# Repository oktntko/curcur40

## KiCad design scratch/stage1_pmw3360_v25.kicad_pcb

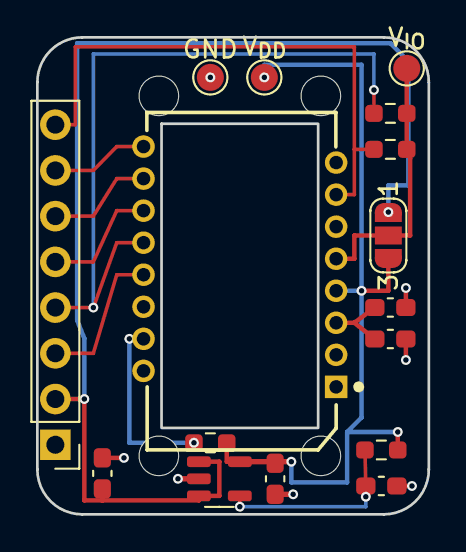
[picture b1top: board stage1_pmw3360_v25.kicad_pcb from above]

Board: 2 copper layers, 21.8 x 26.5 mm, 20 parts (0 on the bottom side), 13 nets.

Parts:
C1: 4.7uF/10V; C_0603_1608Metric_Pad1.08x0.95mm_HandSolder
C2: 100nF; C_0603_1608Metric_Pad1.08x0.95mm_HandSolder
C3, C4: 1uF; C_0603_1608Metric_Pad1.08x0.95mm_HandSolder
C5: 22nF; C_0603_1608Metric_Pad1.08x0.95mm_HandSolder
H1, H2, H3, H4: MountingHole_2.2mm_M2
J1: Conn_01x08; PinHeader_1x08_P2.54mm_Vertical
JP1: SolderJumper_3_Open; SolderJumper-3_P1.3mm_Open_RoundedPad1.0x1.5mm_NumberLabels
R1, R2: 10k; R_0603_1608Metric_Pad0.98x0.95mm_HandSolder
R3: 39R; R_0603_1608Metric_Pad0.98x0.95mm_HandSolder
R4: 28k; R_0603_1608Metric_Pad0.98x0.95mm_HandSolder
TP1: VIO; TestPoint_Pad_D1.5mm
TP2: VDD; TestPoint_Pad_D1.5mm
TP3: GND; TestPoint_Pad_D1.5mm
U1: PMW3360DM-T2QU; PMW3360DM-T2QU_16Pin
U2: TLV74318PDBVR; SOT-23-5

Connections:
/CS: J1.3, U1.13 (~CS)
/MISO: J1.4, R2.2, U1.12 (MISO)
/MOSI: J1.5, U1.11 (MOSI)
/MOTION: J1.7, U1.9 (MOTION)
/RESET: J1.8, R1.2, U1.7 (~RESET)
/SCLK: J1.6, U1.10 (SCLK)
GND: C1.2, C2.2, C3.2, C4.2, C5.2, J1.1, TP3.1, U1.8 (GND), U2.2 (GND)
unnamed: R3.2, U1.15 (LED_P)
unnamed: C1.1, C2.1, U1.3 (VDDPIX)
unnamed: C5.1, R4.2, U2.4 (NC)
VDD: C4.1, JP1.3 (B), R3.1, R4.1, TP2.1, U1.4 (VDD), U2.5 (OUT)
V_{IN}: C3.1, J1.2, JP1.1 (A), U2.1 (IN), U2.3 (EN)
V_{IO}: JP1.2 (C), R1.1, R2.1, TP1.1, U1.5 (VDDIO)

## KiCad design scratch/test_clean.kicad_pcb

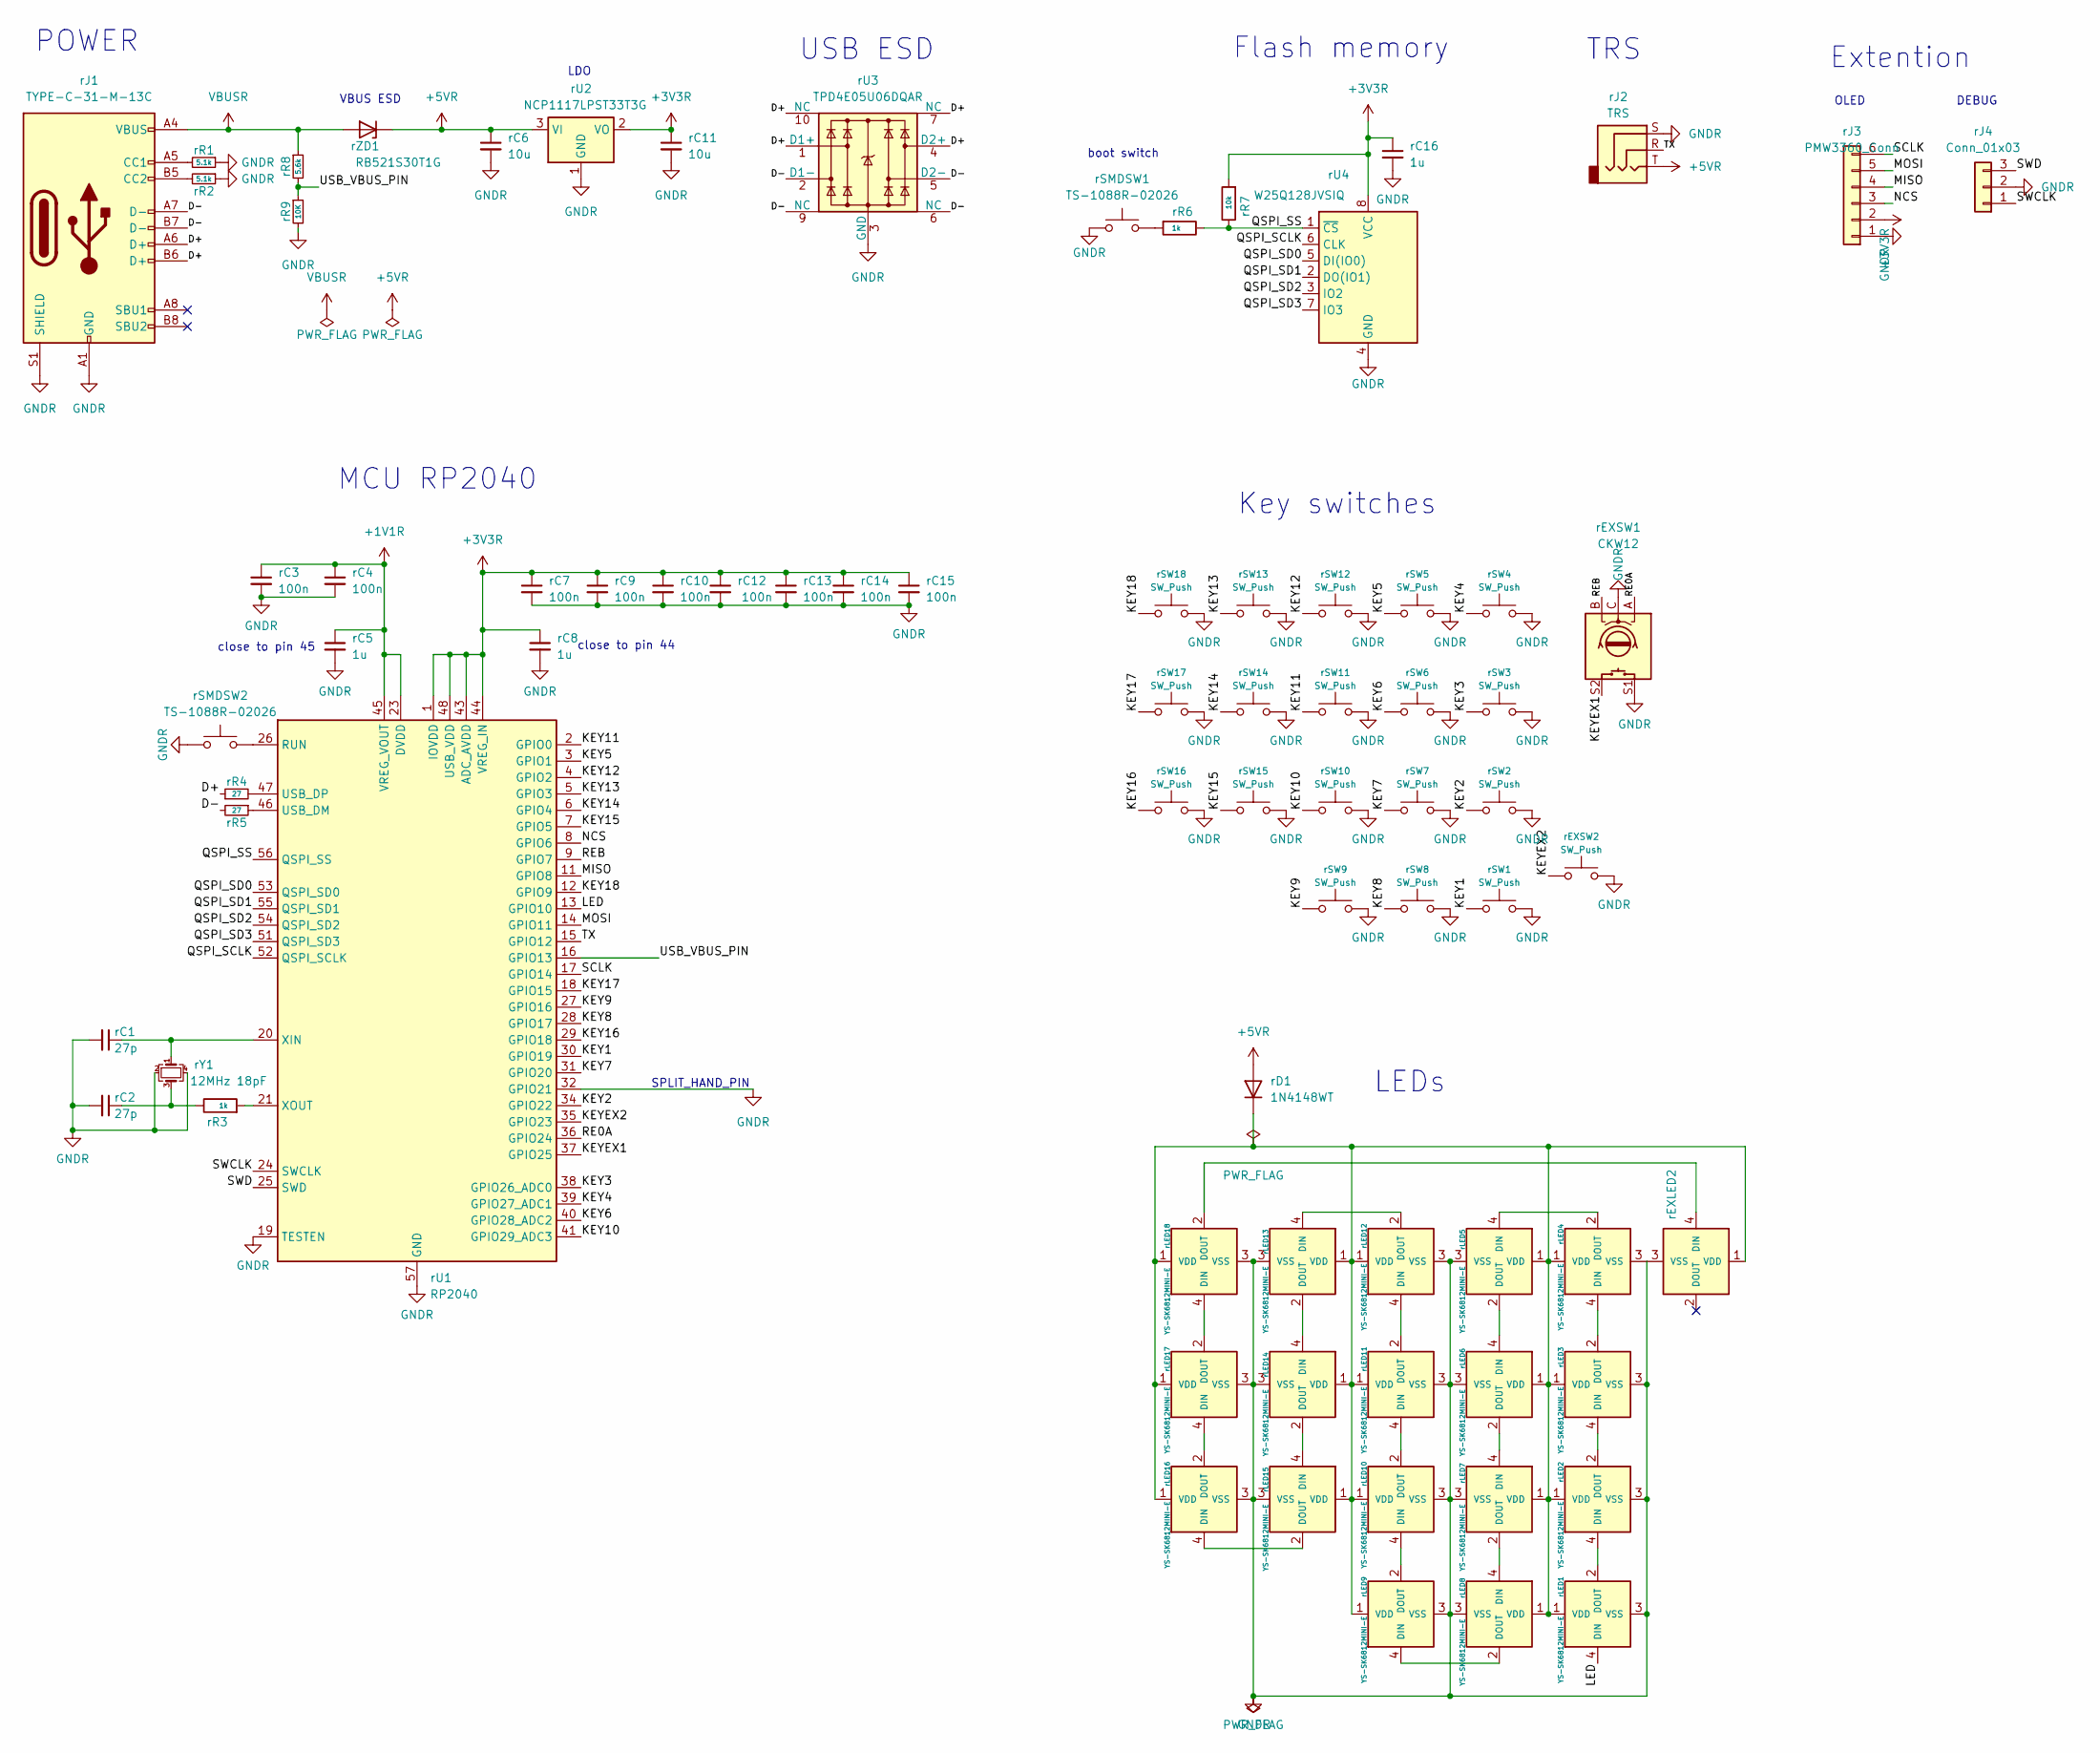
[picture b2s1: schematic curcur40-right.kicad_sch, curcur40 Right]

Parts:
rC1, rC2: 27p; C_0402_1005Metric
rC3, rC4, rC7, rC9, rC10, rC12, rC13, rC14, rC15: 100n; C_0402_1005Metric
rC5, rC8, rC16: 1u; C_0402_1005Metric
rC6, rC11: 10u; C_0402_1005Metric
rD1: 1N4148WT; D_SOD-523; JLCPCB Part # C232841
rEXLED2: YS-SK6812MINI-E
rEXSW1: CKW12
rEXSW2: SW_Push; keyswitch_choc12_hotswap_1u
rJ1: TYPE-C-31-M-13C; JLCPCB Part # C2848620
rJ2: TRS; PJ-398A-5A_PJ-399B-6A; JLCPCB Part # C128994
rJ3: PMW3360_Conn; PinHeader_1x06_P2.54mm_Vertical
rJ4: Conn_01x03; PinHeader_1x03_P2.54mm_Vertical
rLED1, rLED2, rLED3, rLED4, rLED5, rLED6, rLED7, rLED8, rLED9, rLED10, rLED11, rLED12, rLED13, rLED14, rLED15, rLED16, rLED17, rLED18: YS-SK6812MINI-E
rR1, rR2: 5.1k; R_0402_1005Metric
rR3, rR6: 1k; R_0402_1005Metric
rR4, rR5: 27; R_0402_1005Metric
rR7: 10k; R_0402_1005Metric
rR8: 5.6k; R_0402_1005Metric
rR9: 10K; R_0402_1005Metric
rSMDSW1, rSMDSW2: TS-1088R-02026; JLCPCB Part # C455280
rSW1, rSW2, rSW3, rSW4, rSW5, rSW6, rSW7, rSW8, rSW9, rSW10, rSW11, rSW12, rSW13, rSW14, rSW15, rSW16, rSW17, rSW18: SW_Push; keyswitch_choc12_hotswap_1u
rU1: RP2040; QFN-56-1EP_7x7mm_P0.4mm_EP3.2x3.2mm; JLCPCB Part # C2040
rU2: NCP1117LPST33T3G; SOT-223-3_TabPin2; JLCPCB Part # C146799
rU3: TPD4E05U06DQAR; USON-10_2.5x1.0mm_P0.5mm; JLCPCB Part # C138714
rU4: W25Q128JVSIQ; SOIC-8_5.3x5.3mm_P1.27mm; JLCPCB Part # C113767
rY1: 12MHz 18pF; Crystal_SMD_3225-4Pin_3.2x2.5mm; MFR.Part # Q22FA23V0041800; JLCPCB Part # C91749
rZD1: RB521S30T1G; D_SOD-523; JLCPCB Part # C145179

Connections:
+1V1R: rC3.1, rC4.1, rC5.1, rU1.23 (DVDD), rU1.45 (VREG_VOUT), rU1.50 (DVDD)
+3V3R: rC7.1, rC8.1, rC9.1, rC10.1, rC11.1, rC12.1, rC13.1, rC14.1, rC15.1, rC16.1, rJ3.2, rR7.2, rU1.1 (IOVDD), rU1.10 (IOVDD), rU1.22 (IOVDD), rU1.33 (IOVDD), rU1.42 (IOVDD), rU1.43 (ADC_AVDD), rU1.44 (VREG_IN), rU1.48 (USB_VDD), rU1.49 (IOVDD), rU2.2 (VO), rU4.8 (VCC); also elsewhere on the board
+5VR: rC6.1, rD1.2 (A), rJ2.T, rU2.3 (VI), rZD1.1 (K)
/D+: rJ1.A6 (D+), rJ1.B6 (D+), rR4.1, rU3.1 (D1+), rU3.4 (D2+), rU3.7 (NC), rU3.10 (NC)
/D-: rJ1.A7 (D-), rJ1.B7 (D-), rR5.2, rU3.2 (D1-), rU3.5 (D2-), rU3.6 (NC), rU3.9 (NC)
/KEY1: rSW1.1, rU1.30 (GPIO19)
/KEY2: rSW2.1, rU1.34 (GPIO22)
/KEY3: rSW3.1, rU1.38 (GPIO26_ADC0)
/KEY4: rSW4.1, rU1.39 (GPIO27_ADC1)
/KEY5: rSW5.1, rU1.3 (GPIO1)
/KEY6: rSW6.1, rU1.40 (GPIO28_ADC2)
/KEY7: rSW7.1, rU1.31 (GPIO20)
/KEY8: rSW8.1, rU1.28 (GPIO17)
/KEY9: rSW9.1, rU1.27 (GPIO16)
/KEY10: rSW10.1, rU1.41 (GPIO29_ADC3)
/KEY11: rSW11.1, rU1.2 (GPIO0)
/KEY12: rSW12.1, rU1.4 (GPIO2)
/KEY13: rSW13.1, rU1.5 (GPIO3)
/KEY14: rSW14.1, rU1.6 (GPIO4)
/KEY15: rSW15.1, rU1.7 (GPIO5)
/KEY16: rSW16.1, rU1.29 (GPIO18)
/KEY17: rSW17.1, rU1.18 (GPIO15)
/KEY18: rSW18.1, rU1.12 (GPIO9)
/KEYEX1: rEXSW1.S2, rU1.37 (GPIO25)
/KEYEX2: rEXSW2.1, rU1.35 (GPIO23)
/LED: rLED1.4 (DIN), rU1.13 (GPIO10)
/MISO: rJ3.4, rU1.11 (GPIO8); also elsewhere on the board
/MOSI: rJ3.5, rU1.14 (GPIO11); also elsewhere on the board
/NCS: rJ3.3, rU1.8 (GPIO6); also elsewhere on the board
/QSPI_SCLK: rU1.52 (QSPI_SCLK), rU4.6 (CLK)
/QSPI_SD0: rU1.53 (QSPI_SD0), rU4.5 (DI(IO0))
/QSPI_SD1: rU1.55 (QSPI_SD1), rU4.2 (DO(IO1))
/QSPI_SD2: rU1.54 (QSPI_SD2), rU4.3 (IO2)
/QSPI_SD3: rU1.51 (QSPI_SD3), rU4.7 (IO3)
/QSPI_SS: rR6.1, rR7.1, rU1.56 (QSPI_SS), rU4.1 (~CS)
/RE0A: rEXSW1.A, rU1.36 (GPIO24)
/REB: rEXSW1.B, rU1.9 (GPIO7)
/SCLK: rJ3.6, rU1.17 (GPIO14); also elsewhere on the board
/SWCLK: rJ4.1, rU1.24 (SWCLK)
/SWD: rJ4.3, rU1.25 (SWD)
/TX: rJ2.R, rU1.15 (GPIO12)
/USB_VBUS_PIN: rR8.2, rR9.1, rU1.16 (GPIO13)
GNDR: rC1.2, rC2.2, rC3.2, rC4.2, rC5.2, rC6.2, rC7.2, rC8.2, rC9.2, rC10.2, rC11.2, rC12.2, rC13.2, rC14.2, rC15.2, rC16.2, rEXLED2.3 (VSS), rEXSW1.C, rEXSW1.S1, rEXSW2.2, rJ1.A1 (GND), rJ1.A12 (GND), rJ1.B1 (GND), rJ1.B12 (GND), rJ1.S1 (SHIELD), rJ2.S, rJ3.1, rJ4.2, rLED1.3 (VSS), rLED2.3 (VSS), rLED3.3 (VSS), rLED4.3 (VSS), rLED5.3 (VSS), rLED6.3 (VSS), rLED7.3 (VSS), rLED8.3 (VSS), rLED9.3 (VSS), rLED10.3 (VSS), rLED11.3 (VSS), rLED12.3 (VSS), rLED13.3 (VSS), rLED14.3 (VSS), rLED15.3 (VSS), rLED16.3 (VSS), rLED17.3 (VSS), rLED18.3 (VSS), rR1.1, rR2.1, rR9.2, rSMDSW1.1, rSMDSW2.1, rSW1.2, rSW2.2, rSW3.2, rSW4.2, rSW5.2, rSW6.2, rSW7.2, rSW8.2, rSW9.2, rSW10.2, rSW11.2, rSW12.2, rSW13.2, rSW14.2, rSW15.2, rSW16.2, rSW17.2, rSW18.2, rU1.19 (TESTEN), rU1.32 (GPIO21), rU1.57 (GND), rU2.1 (GND), rU3.3 (GND), rU3.8 (GND), rU4.4 (GND), rY1.2, rY1.4; also elsewhere on the board
unnamed: rC2.1, rR3.1, rY1.3
unnamed: rD1.1 (K), rEXLED2.1 (VDD), rLED1.1 (VDD), rLED2.1 (VDD), rLED3.1 (VDD), rLED4.1 (VDD), rLED5.1 (VDD), rLED6.1 (VDD), rLED7.1 (VDD), rLED8.1 (VDD), rLED9.1 (VDD), rLED10.1 (VDD), rLED11.1 (VDD), rLED12.1 (VDD), rLED13.1 (VDD), rLED14.1 (VDD), rLED15.1 (VDD), rLED16.1 (VDD), rLED17.1 (VDD), rLED18.1 (VDD)
unnamed: rEXLED2.4 (DIN), rLED18.2 (DOUT)
unnamed: rJ1.A5 (CC1), rR1.2
unnamed: rJ1.B5 (CC2), rR2.2
unnamed: rLED1.2 (DOUT), rLED2.4 (DIN)
unnamed: rLED2.2 (DOUT), rLED3.4 (DIN)
unnamed: rLED3.2 (DOUT), rLED4.4 (DIN)
unnamed: rLED4.2 (DOUT), rLED5.4 (DIN)
unnamed: rLED5.2 (DOUT), rLED6.4 (DIN)
unnamed: rLED6.2 (DOUT), rLED7.4 (DIN)
unnamed: rLED7.2 (DOUT), rLED8.4 (DIN)
unnamed: rLED8.2 (DOUT), rLED9.4 (DIN)
unnamed: rLED9.2 (DOUT), rLED10.4 (DIN)
unnamed: rLED10.2 (DOUT), rLED11.4 (DIN)
unnamed: rLED11.2 (DOUT), rLED12.4 (DIN)
unnamed: rLED12.2 (DOUT), rLED13.4 (DIN)
unnamed: rLED13.2 (DOUT), rLED14.4 (DIN)
unnamed: rLED14.2 (DOUT), rLED15.4 (DIN)
unnamed: rLED15.2 (DOUT), rLED16.4 (DIN)
unnamed: rLED16.2 (DOUT), rLED17.4 (DIN)
unnamed: rLED17.2 (DOUT), rLED18.4 (DIN)
unnamed: rR6.2, rSMDSW1.2
unnamed: rSMDSW2.2, rU1.26 (RUN)
unnamed: rR5.1, rU1.46 (USB_DM)
unnamed: rR4.2, rU1.47 (USB_DP)
unnamed: rC1.1, rU1.20 (XIN), rY1.1
unnamed: rR3.2, rU1.21 (XOUT)
VBUSR: rJ1.A4 (VBUS), rJ1.A9 (VBUS), rJ1.B4 (VBUS), rJ1.B9 (VBUS), rR8.1, rZD1.2 (A)

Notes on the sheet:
USB ESD
TRS
Flash memory
MCU RP2040
DEBUG
POWER
boot switch
LDO
Key switches
LEDs
Extention
VBUS ESD
OLED
close to pin 45
close to pin 44
SPLIT_HAND_PIN

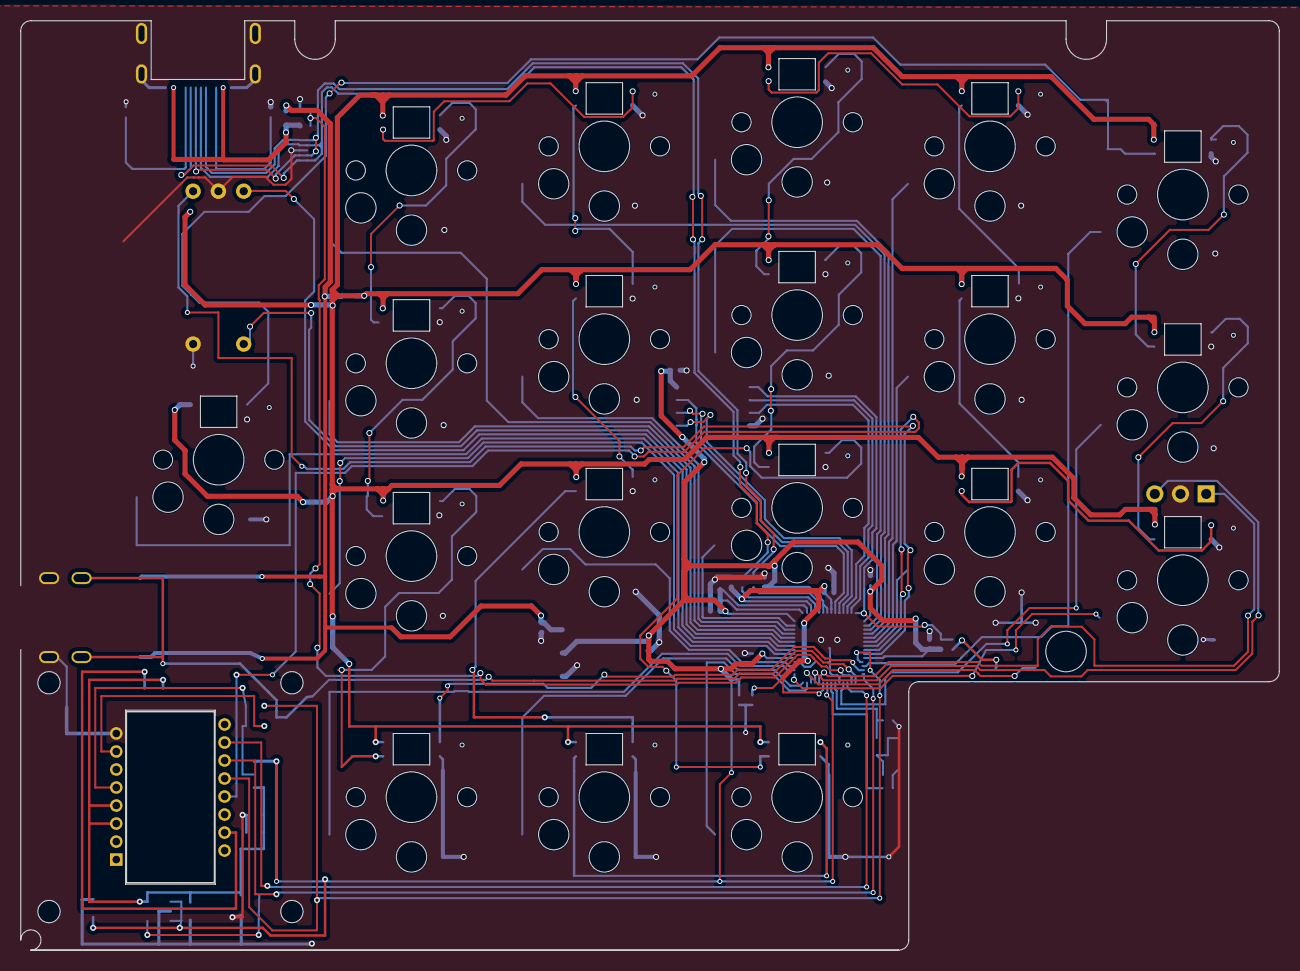
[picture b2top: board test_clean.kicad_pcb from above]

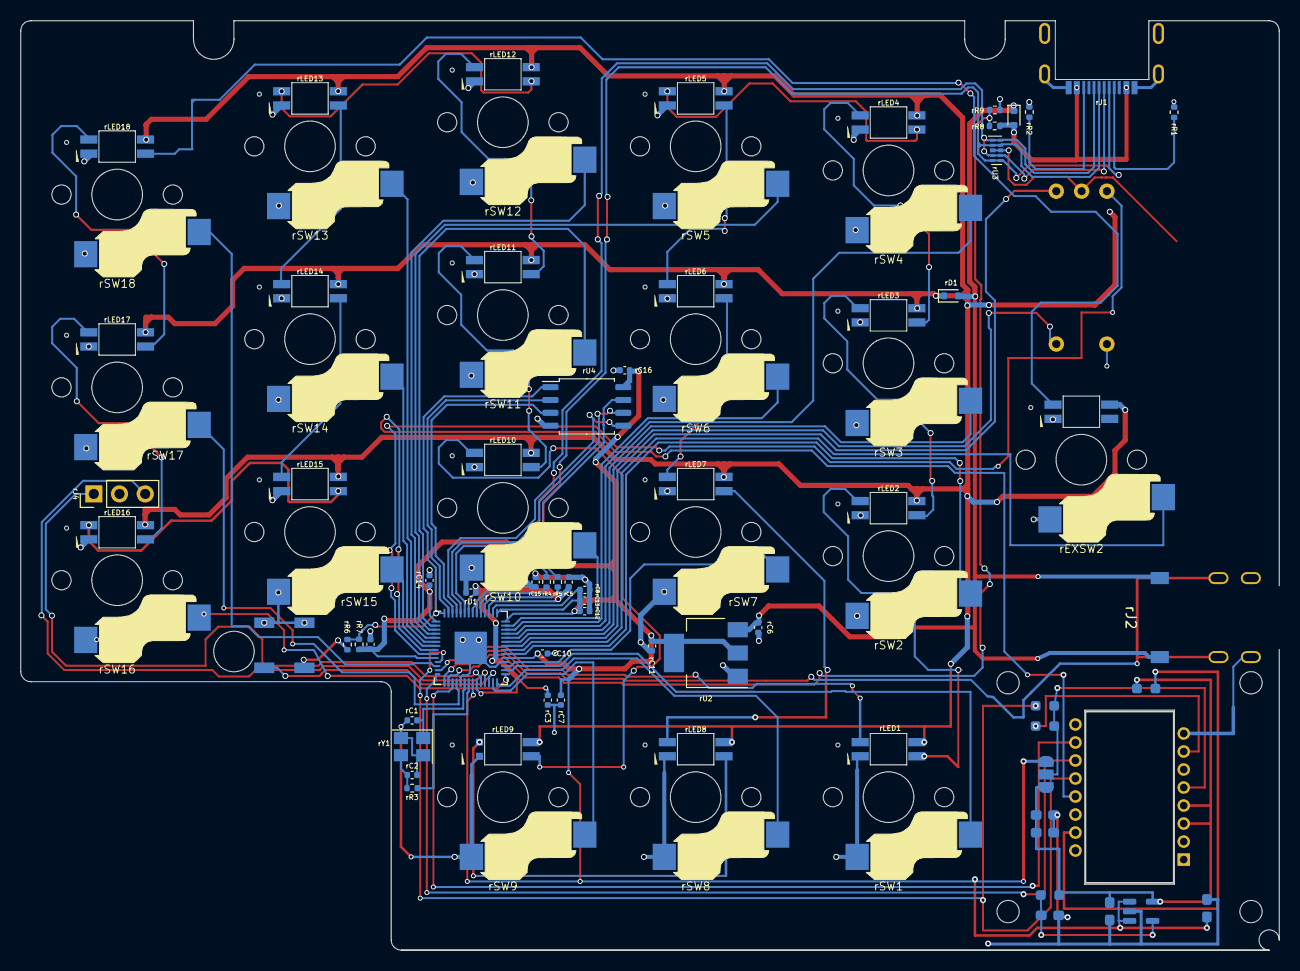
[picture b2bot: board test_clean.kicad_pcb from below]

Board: 2 copper layers, 124.3 x 91.8 mm, 88 parts (87 on the bottom side), 77 nets.

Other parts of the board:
C1: 4.7uF/10V; C_0603_1608Metric_Pad1.08x0.95mm_HandSolder
C2: 100nF; C_0603_1608Metric_Pad1.08x0.95mm_HandSolder
C3, C4: 1uF; C_0603_1608Metric_Pad1.08x0.95mm_HandSolder
C5: 22nF; C_0603_1608Metric_Pad1.08x0.95mm_HandSolder
JP1: SolderJumper_3_Open; SolderJumper-3_P1.3mm_Open_RoundedPad1.0x1.5mm_NumberLabels
R1, R2: 10k; R_0603_1608Metric_Pad0.98x0.95mm_HandSolder
R3: 39R; R_0603_1608Metric_Pad0.98x0.95mm_HandSolder
R4: 28k; R_0603_1608Metric_Pad0.98x0.95mm_HandSolder
U1: PMW3360DM-T2QU; PMW3360DM-T2QU_16Pin
U2: TLV74318PDBVR; SOT-23-5

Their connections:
+1V8_PMW: C1.1, C2.1, C4.1, JP1.3 (B), R3.1, R4.1, U1.3 (VDDPIX), U1.4 (VDD), U2.5 (OUT)
+3V3R: C3.1, JP1.1 (A), U2.1 (IN), U2.3 (EN); also elsewhere on the board
/MISO: R2.2, U1.12 (MISO); also elsewhere on the board
/MOSI: U1.11 (MOSI); also elsewhere on the board
/NCS: U1.13 (~CS); also elsewhere on the board
/RESET: R1.2, U1.7 (~RESET)
/SCLK: U1.10 (SCLK); also elsewhere on the board
GNDR: C1.2, C2.2, C3.2, C4.2, C5.2, U1.8 (GND), U2.2 (GND); also elsewhere on the board
unnamed: R3.2, U1.15 (LED_P)
unnamed: C5.1, R4.2, U2.4 (NC)
V_{IO}: JP1.2 (C), R1.1, R2.1, U1.5 (VDDIO)

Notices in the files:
scratch/stage1_pmw3360_v25.kicad_pcb:
Open Source Hardware, CERN-OHL-P v2
